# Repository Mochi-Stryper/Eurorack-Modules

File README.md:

# Eurorack-Modules
 Eurorack-Modules

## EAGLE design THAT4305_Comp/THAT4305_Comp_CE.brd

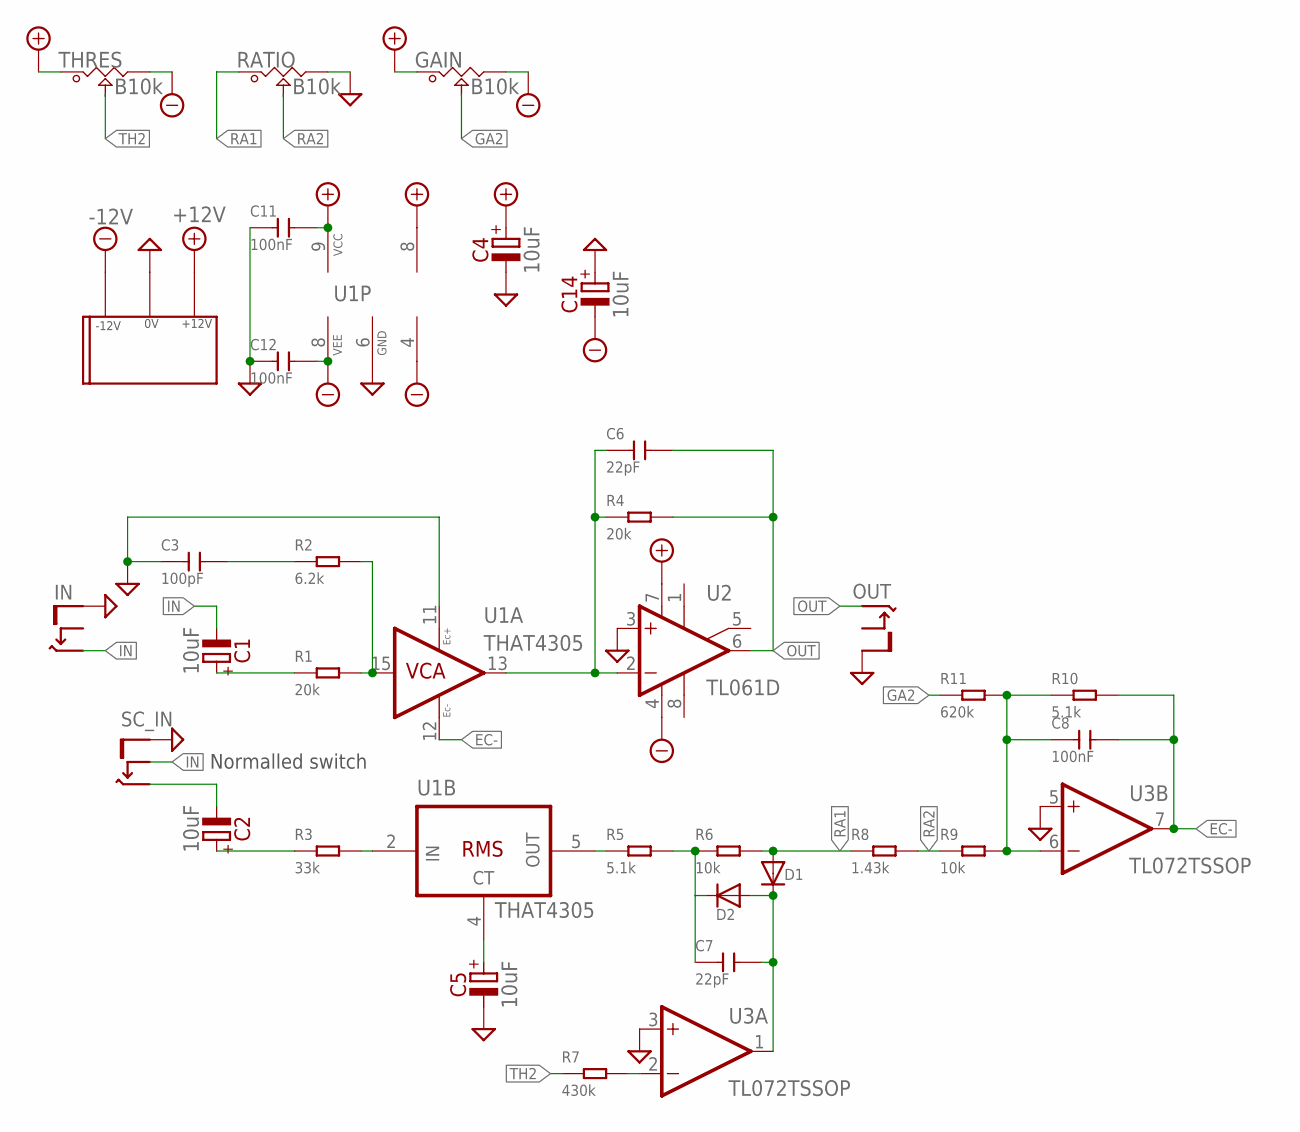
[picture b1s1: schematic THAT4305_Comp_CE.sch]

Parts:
C1, C2, C4, C5, C14: 10uF; PAN_B
C3: 100pF; C0805
C6, C7: 22pF; C0805
C8, C11, C12: 100nF; C0805
D1, D2: DIODESOD-123; SOD-123
GAIN: B10k; POT_9MM_SMD
R1, R4: 20k; R0805
R2: 6.2k; R0805
R3: 33k; R0805
R5, R10: 5.1k; R0805
R6, R9: 10k; R0805
R7: 430k; R0805
R8: 1.43k; R0805
R11: 620k; R0805
RATIO: B10k; POT_9MM_SMD
THRES: B10k; POT_9MM_SMD
U1: THAT4305; QSOP16
U2: TL061D; SO08
U3: TL072TSSOP; TSSOP-8
U$2: EURO_POW_CEH
U$3: THONKICONN_CE_3X_COMG_1SW; 1.27MM_CE_4X_COMG_NOSW

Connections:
+12V: C4.1+ (+), C11.2, GAIN.1, THRES.1, U1.9 (VCC), U2.7 (V+), U3.8 (V+), U$2.+12V
-12V: C12.2, C14.2- (-), GAIN.3, THRES.3, U1.8 (VEE), U2.4 (V-), U3.4 (V-), U$2.-12V
EC-: C8.2, R10.2, U1.12 (EC-), U3.7 (OUT)
GA2: GAIN.2, R11.1
GND: C3.1, C4.2- (-), C5.2- (-), C11.1, C12.1, C14.1+ (+), RATIO.3, U1.6 (GND), U1.11 (EC+), U2.3 (+IN), U3.3 (+IN), U3.5 (+IN), U$2.GND, U$3.0 (S)
IN: C1.2- (-), U$3.2 (SW), U$3.3 (T)
unnamed: C1.1+ (+), R1.1
unnamed: C3.2, R2.1
unnamed: R1.2, R2.2, U1.15 (VCA_IN)
unnamed: C2.1+ (+), R3.1
unnamed: R3.2, U1.2 (RMS_IN)
unnamed: C5.1+ (+), U1.4 (CT)
unnamed: C6.1, R4.1, U1.13 (VCA_OUT), U2.2 (-IN)
unnamed: R5.1, U1.5 (RMS_OUT)
unnamed: C7.1, D2.C, R5.2, R6.1
unnamed: C8.1, R9.2, R10.1, R11.2, U3.6 (-IN)
unnamed: C7.2, D1.C, D2.A, U3.1 (OUT)
unnamed: R7.2, U3.2 (-IN)
OUT: C6.2, R4.2, U2.6 (OUT), U$3.4 (T)
RA1: D1.A, R6.2, R8.1, RATIO.1
RA2: R8.2, R9.1, RATIO.2
SC_IN: C2.2- (-), U$3.1 (T)
TH2: R7.1, THRES.2

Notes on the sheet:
SC_IN
OUT
Normalled switch

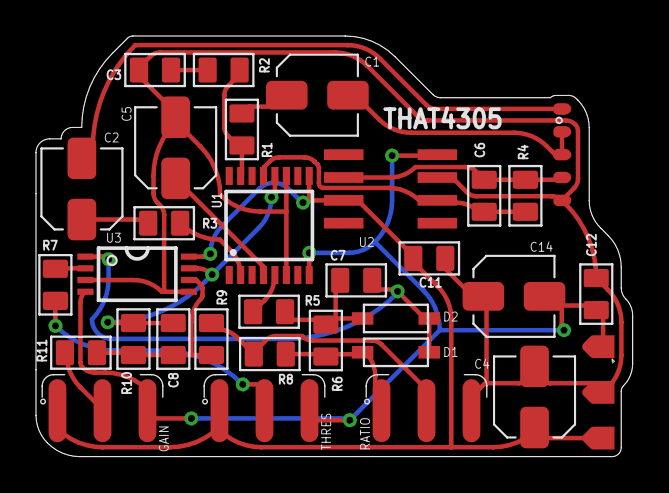
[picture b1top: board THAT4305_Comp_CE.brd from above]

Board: 2 copper layers, 33.1 x 23.4 mm, 32 parts (0 on the bottom side), 23 nets.

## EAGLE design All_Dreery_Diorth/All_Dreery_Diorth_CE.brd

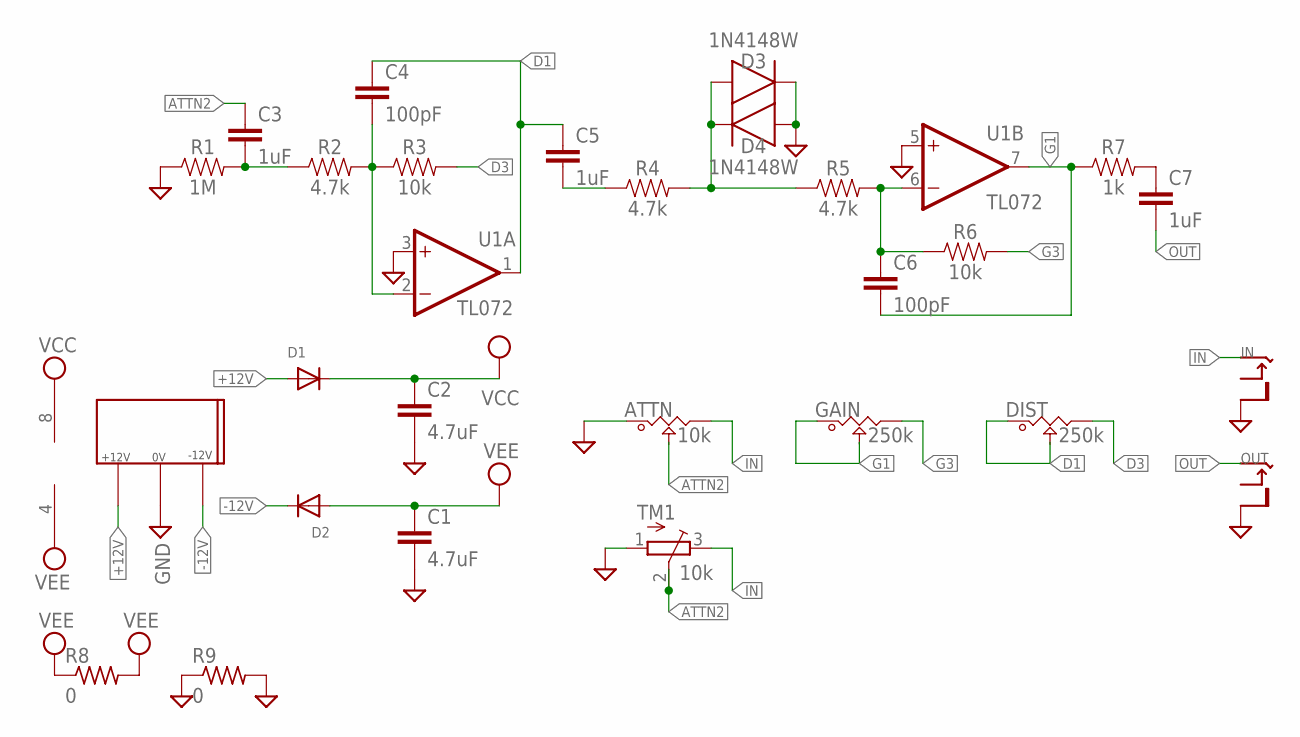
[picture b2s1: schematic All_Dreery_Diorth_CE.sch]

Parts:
ATTN: 10k; POT_9MM_SMD
C1, C2: 4.7uF; 1206
C3, C5, C7: 1uF; 0603
C4, C6: 100pF; 0603
D1, D2: DIODESOD-123; SOD-123
D3, D4: 1N4148W; SOD3715X135
DIST: 250k; POT_9MM_SMD
GAIN: 250k; POT_9MM_SMD
R1: 1M; 0603
R2, R4, R5: 4.7k; 0603
R3, R6: 10k; 0603
R7: 1k; 0603
R8, R9: 0; R0402
TM1: 10k; TC33X
U1: TL072; TSSOP-8
U$1: EURO_POW_CEH
U$2: THONKICONN_CE_2X_COMG_NOSW; 1.27MM_CE_2X_COMG_NOSW

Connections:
+12V: D1.A, U$1.+12V
-12V: D2.C, U$1.-12V
ATTN2: ATTN.2, C3.1, TM1.2 (S)
D1: C4.1, C5.1, DIST.1, DIST.2, U1.1 (OUT)
D3: DIST.3, R3.2
G1: C6.2, GAIN.1, GAIN.2, R7.1, U1.7 (OUT)
G3: GAIN.3, R6.2
GND: ATTN.1, C1.2, C2.2, D3.1 (C), D4.2 (A), R1.1, R9.1, R9.2, TM1.1 (A), U1.3 (+IN), U1.5 (+IN), U$1.GND, U$2.0 (S)
IN: ATTN.3, TM1.3 (E), U$2.1 (T)
unnamed: C3.2, R1.2, R2.1
unnamed: C4.2, R2.2, R3.1, U1.2 (-IN)
unnamed: C7.1, R7.2
unnamed: C5.2, R4.1
unnamed: D3.2 (A), D4.1 (C), R4.2, R5.1
unnamed: C6.1, R5.2, R6.1, U1.6 (-IN)
OUT: C7.2, U$2.2 (T)
VCC: C2.1, D1.C, U1.8 (V+)
VEE: C1.1, D2.A, R8.1, R8.2, U1.4 (V-)

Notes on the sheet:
OUT

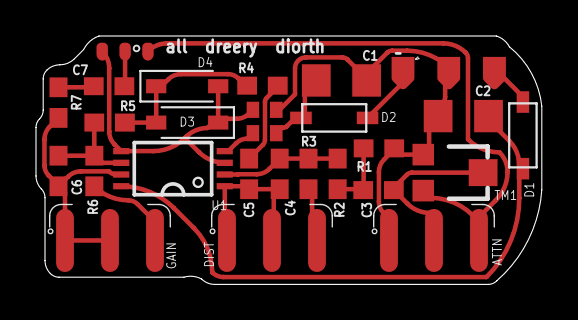
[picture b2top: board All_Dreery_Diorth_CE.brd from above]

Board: 2 copper layers, 28.1 x 13.8 mm, 27 parts (0 on the bottom side), 18 nets.

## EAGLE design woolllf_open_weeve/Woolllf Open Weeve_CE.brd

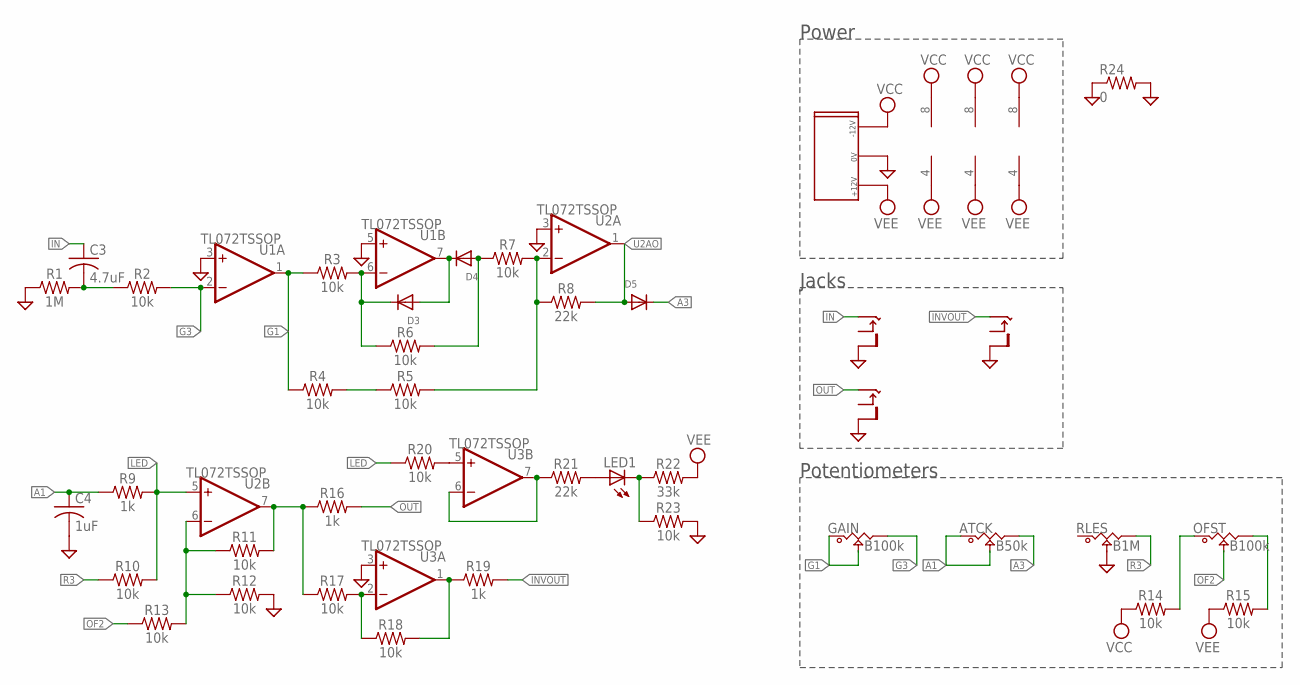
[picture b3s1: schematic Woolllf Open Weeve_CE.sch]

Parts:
ATCK: B50k; POT_9MM_SMD
C3: 4.7uF; C0603
C4: 1uF; C0603
D3, D4, D5: DIODESOD-123; SOD-123
GAIN: B100k; POT_9MM_SMD
LED1: LEDCHIP-LED0603; CHIP-LED0603
OFST: B100k; POT_9MM_SMD
R1: 1M; 0603
R2, R3, R4, R5, R6, R7, R10, R11, R12, R13, R14, R15, R17, R18, R20, R23: 10k; 0603
R8, R21: 22k; 0603
R9, R16, R19: 1k; 0603
R22: 33k; 0603
R24: 0; R0402
RLES: B1M; POT_9MM_SMD
U1, U2, U3: TL072TSSOP; TSSOP-8
U$1: EURO_POW_CEH
U$2: THONKICONN_CE_3X_COMG_NOSW; 1.27MM_CE_3X_COMG_NOSW

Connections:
A1: ATCK.1, ATCK.2, C4.1, R9.1
A3: ATCK.3, D5.C
G1: GAIN.1, GAIN.2, R3.1, R4.1, U1.1 (OUT)
G3: GAIN.3, R2.2, U1.2 (-IN)
GND: C4.2, R1.1, R12.2, R23.2, R24.1, R24.2, RLES.2, U1.3 (+IN), U1.5 (+IN), U2.3 (+IN), U3.3 (+IN), U$1.GND, U$2.0 (S)
IN: C3.1, U$2.1 (T)
INVOUT: R19.2, U$2.2 (T)
LED: R9.2, R10.2, R20.1, U2.5 (+IN)
unnamed: LED1.A, R21.2
unnamed: C3.2, R1.2, R2.1
unnamed: D3.C, R3.2, R6.1, U1.6 (-IN)
unnamed: D3.A, D4.C, U1.7 (OUT)
unnamed: D4.A, R6.2, R7.1
unnamed: R20.2, U3.5 (+IN)
unnamed: R4.2, R5.1
unnamed: R5.2, R7.2, R8.1, U2.2 (-IN)
unnamed: R11.1, R12.1, R13.2, U2.6 (-IN)
unnamed: R11.2, R16.1, R17.1, U2.7 (OUT)
unnamed: OFST.1, R14.2
unnamed: OFST.3, R15.2
unnamed: R17.2, R18.1, U3.2 (-IN)
unnamed: R18.2, R19.1, U3.1 (OUT)
unnamed: R21.1, U3.6 (-IN), U3.7 (OUT)
unnamed: LED1.C, R22.1, R23.1
OF2: OFST.2, R13.1
OUT: R16.2, U$2.3 (T)
R3: R10.1, RLES.3
U2AO: D5.A, R8.2, U2.1 (OUT)
VCC: R14.1, U1.8 (V+), U2.8 (V+), U3.8 (V+), U$1.-12V
VEE: R15.1, R22.2, U1.4 (V-), U2.4 (V-), U3.4 (V-), U$1.+12V

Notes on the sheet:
Power
Jacks
Potentiometers

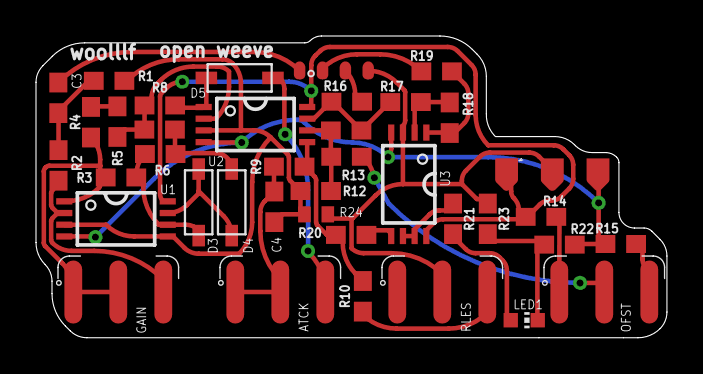
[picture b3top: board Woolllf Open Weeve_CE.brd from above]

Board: 2 copper layers, 35.1 x 16.8 mm, 39 parts (0 on the bottom side), 30 nets.

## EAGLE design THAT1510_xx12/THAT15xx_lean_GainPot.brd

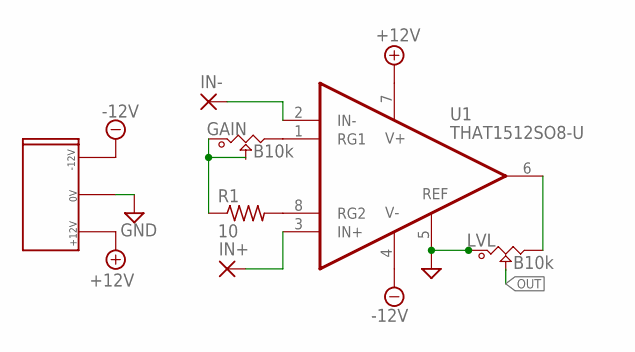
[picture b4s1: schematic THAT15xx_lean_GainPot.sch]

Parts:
GAIN: B10k; POT_9MM_SMD
IN+: WIREPADSMD5-1,8; 5-1,8
IN-: WIREPADSMD5-1,8; 5-1,8
LVL: B10k; POT_9MM_SMD
R1: 10; R0603
U1: THAT1512SO8-U; SO08
U$1: EURO_POW_CEH

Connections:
15XXO: LVL.3, U1.6 (OUT)
+12V: U1.7 (V+), U$1.+12V
-12V: U1.4 (V-), U$1.-12V
GND: LVL.1, U1.5 (REF), U$1.GND
IN+: IN+.1, U1.3 (IN+)
IN-: IN-.1, U1.2 (IN-)
unnamed: R1.2, U1.8 (RG2)
unnamed: GAIN.3, U1.1 (RG1)
unnamed: GAIN.1, GAIN.2, R1.1
OUT: LVL.2

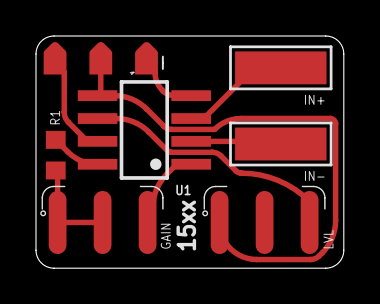
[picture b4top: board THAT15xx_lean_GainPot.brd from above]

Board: 2 copper layers, 17.1 x 12.9 mm, 7 parts (0 on the bottom side), 9 nets.

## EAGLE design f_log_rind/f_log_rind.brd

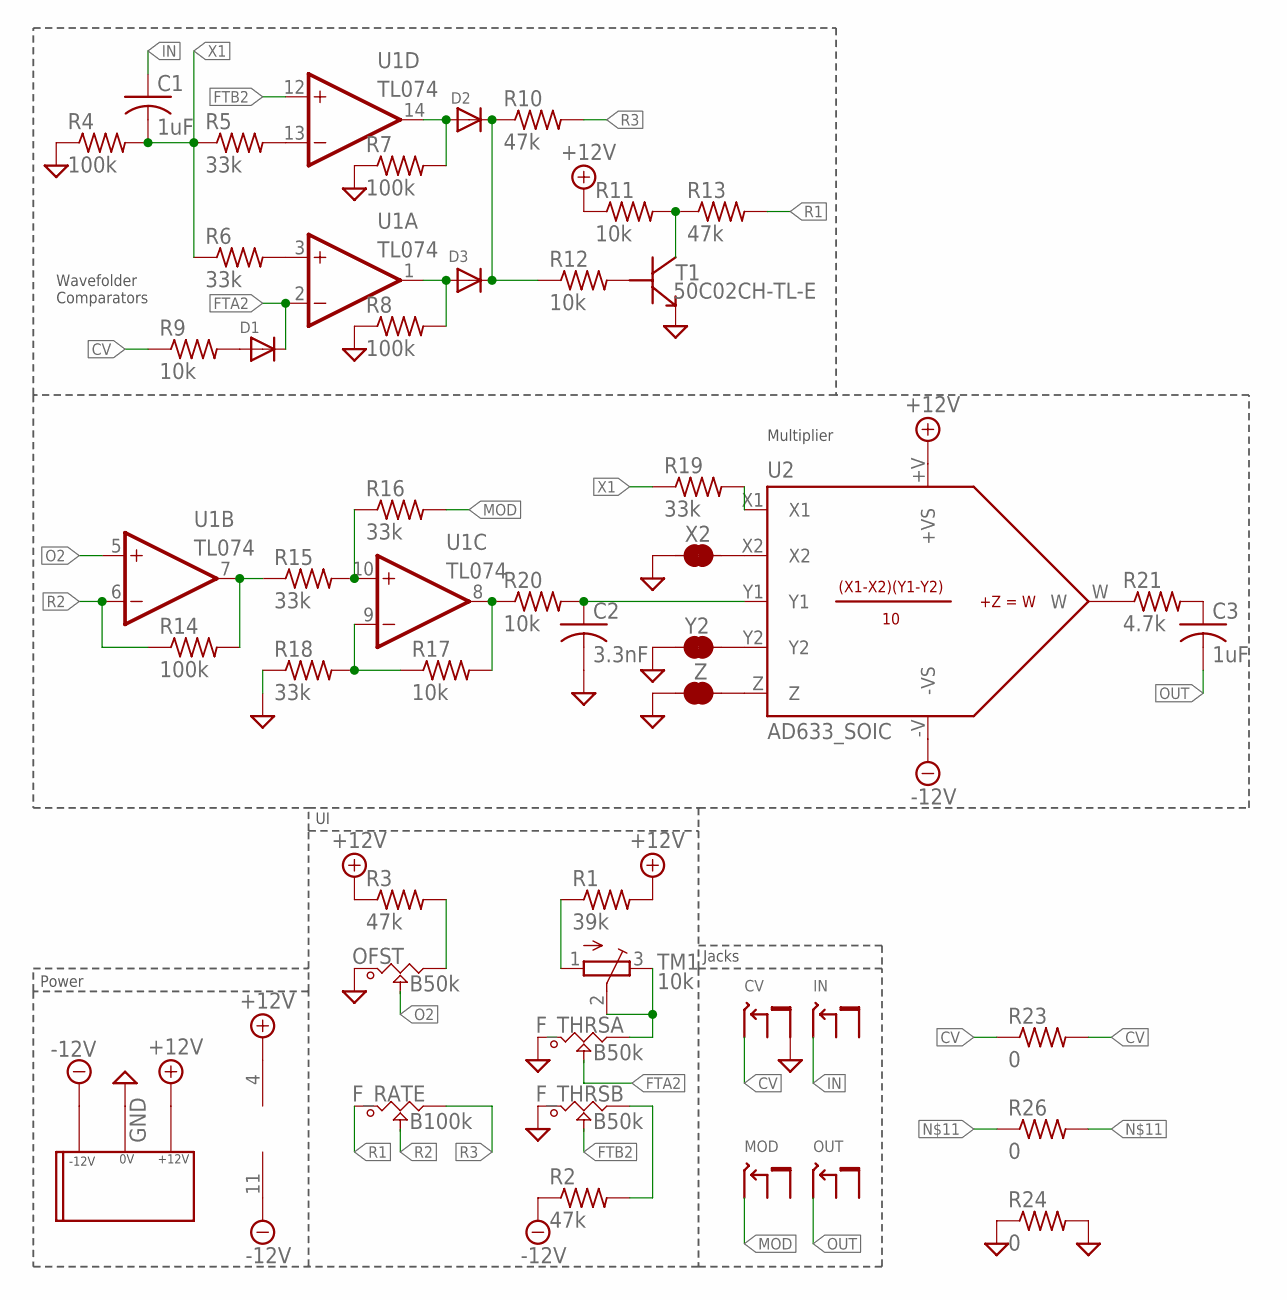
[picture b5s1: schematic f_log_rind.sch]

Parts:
C1, C3: 1uF; C0603
C2: 3.3nF; C0603
D1, D2, D3: DIODESOD-123; SOD-123
F_RATE: B100k; POT_9MM_SMD
F_THRSA: B50k; POT_9MM_SMD
F_THRSB: B50k; POT_9MM_SMD
J_A1: THONKICONN_CE_4X_COMG_NOSW; 1.27MM_CE_4X_COMG_NOSW
OFST: B50k; POT_9MM_SMD
R1: 39k; R0603
R2, R3, R10, R13: 47k; R0603
R4, R7, R8, R14: 100k; R0603
R5, R6, R15, R16, R18, R19: 33k; R0603
R9, R11, R12, R17, R20: 10k; R0603
R21: 4.7k; R0603
R23, R24, R26: 0; R0402
T1: 50C02CH-TL-E; BEC
TM1: 10k; TC33X
U1: TL074; SO14
U2: AD633_SOIC; SOIC_8
U$1: EURO_POW_CEH
X2: JUMPER-SMT_2_NC_TRACE_NO-SILK; SMT-JUMPER_2_NC_TRACE_NO-SILK
Y2: JUMPER-SMT_2_NC_TRACE_NO-SILK; SMT-JUMPER_2_NC_TRACE_NO-SILK
Z: JUMPER-SMT_2_NC_TRACE_NO-SILK; SMT-JUMPER_2_NC_TRACE_NO-SILK

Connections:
+12V: R1.2, R3.1, R11.1, U1.4 (V+), U2.+V (+VS), U$1.+12V
-12V: R2.1, U1.11 (V-), U2.-V (-VS), U$1.-12V
A1A+: R6.2, U1.3 (+IN)
A1AO: D3.A, R8.2, U1.1 (OUT)
A1BO: R14.2, R15.1, U1.7 (OUT)
A1C+: R15.2, R16.1, U1.10 (+IN)
A1C-: R17.1, R18.2, U1.9 (-IN)
A1CO: R17.2, R20.1, U1.8 (OUT)
A1D-: R5.2, U1.13 (-IN)
A1DO: D2.A, R7.2, U1.14 (OUT)
CV: J_A1.1 (T), R9.1, R23.1, R23.2
FTA2: D1.C, F_THRSA.2, U1.2 (-IN)
FTB2: F_THRSB.2, U1.12 (+IN)
GND: C2.2, F_THRSA.1, F_THRSB.1, J_A1.0 (S), OFST.1, R4.1, R7.1, R8.1, R18.1, R24.1, R24.2, T1.E, U$1.GND, X2.1, Y2.1, Z.1
IN: C1.1, J_A1.2 (T)
MOD: J_A1.3 (T), R16.2
unnamed: F_THRSA.3, TM1.2 (S), TM1.3 (E)
unnamed: R1.1, TM1.1 (A)
unnamed: F_THRSB.3, R2.2
unnamed: OFST.3, R3.2
unnamed: U2.Z, Z.2
unnamed: R21.1, U2.W
unnamed: C3.1, R21.2
unnamed: D1.A, R9.2
unnamed: D2.C, D3.C, R10.1, R12.1, R26.1, R26.2
unnamed: R12.2, T1.B
unnamed: R11.2, R13.1, T1.C
unnamed: U2.Y2, Y2.2
unnamed: U2.X2, X2.2
unnamed: R19.2, U2.X1
O2: OFST.2, U1.5 (+IN)
OUT: C3.2, J_A1.4 (T)
R1: F_RATE.1, R13.2
R2: F_RATE.2, R14.1, U1.6 (-IN)
R3: F_RATE.3, R10.2
X1: C1.2, R4.2, R5.1, R6.1, R19.1
Y1: C2.1, R20.2, U2.Y1

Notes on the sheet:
MOD
OUT
Power
Jacks
Wavefolder Comparators
Multiplier

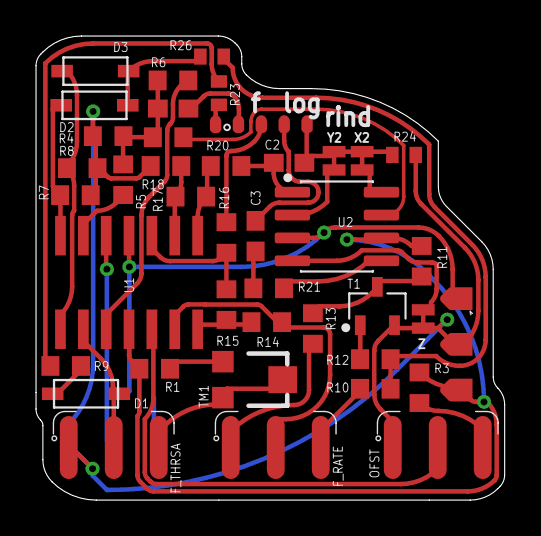
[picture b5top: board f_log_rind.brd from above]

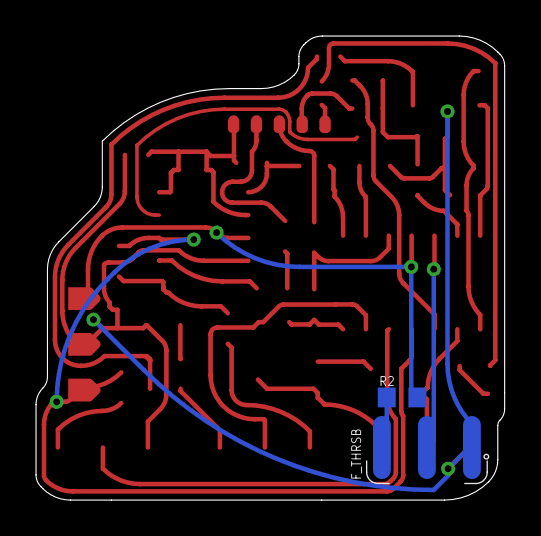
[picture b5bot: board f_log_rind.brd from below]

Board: 2 copper layers, 26.0 x 25.8 mm, 43 parts (2 on the bottom side), 37 nets.

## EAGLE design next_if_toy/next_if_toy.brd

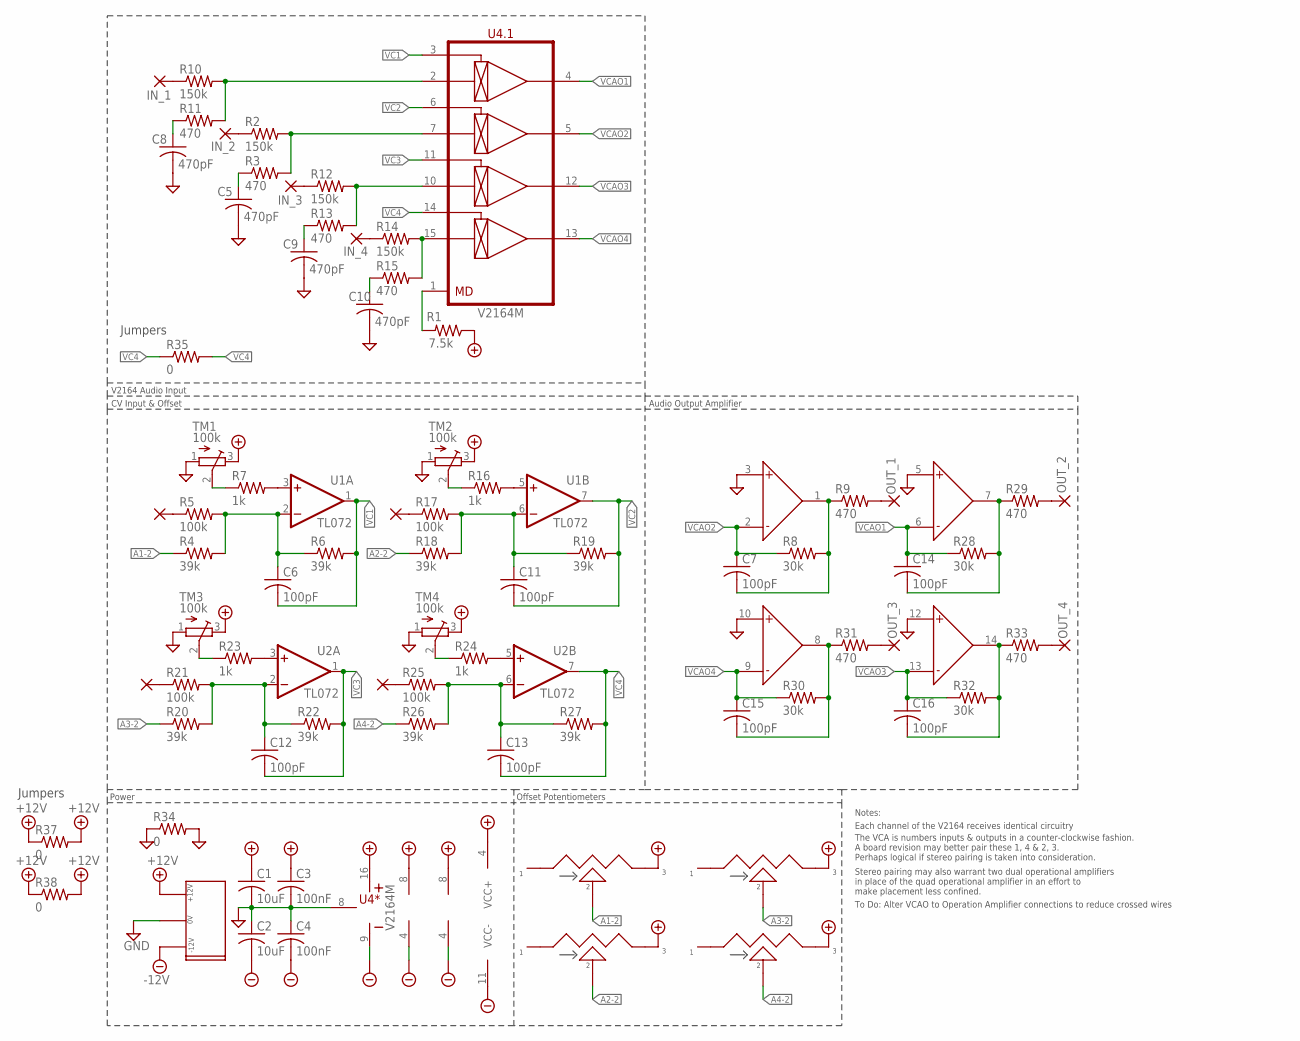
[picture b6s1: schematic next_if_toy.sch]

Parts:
AMT1, AMT2, AMT3, AMT4: B50k; POT_9MM_SMD
C1, C2: 10uF; C1206
C3, C4: 100nF; C0603
C5, C8, C9, C10: 470pF; C0603
C6, C7, C11, C12, C13, C14, C15, C16: 100pF; C0603
CV1, CV2, CV3, CV4: SMD2; SMD1,27-2,54
I1, I2, I3, I4: SMD2; SMD1,27-2,54
O1, O2, O3, O4: SMD2; SMD1,27-2,54
R1: 7.5k; R0603
R2, R10, R12, R14: 150k; R0603
R3, R9, R11, R13, R15, R29, R31, R33: 470; R0603
R4, R6, R18, R19, R20, R22, R26, R27: 39k; R0603
R5, R17, R21, R25: 100k; R0603
R7, R16, R23, R24: 1k; R0603
R8, R28, R30, R32: 30k; R0603
R34, R35, R37, R38: 0; R0402
TM1, TM2, TM3, TM4: 100k; TC33X
U1, U2: TL072; TSSOP-8
U3: TL074TSSOP-14
U4: V2164M; SO-16
U$2: EURO_POW_CEH

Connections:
+12V: AMT1.3, AMT2.3, AMT3.3, AMT4.3, C1.1, C3.1, R1.1, R37.1, R37.2, R38.1, R38.2, TM1.3 (E), TM2.3 (E), TM3.3 (E), TM4.3 (E), U1.8 (V+), U2.8 (V+), U3.4 (VCC+), U4.16 (V+), U$2.+12V
-12V: C2.2, C4.2, U1.4 (V-), U2.4 (V-), U3.11 (VCC-), U4.9 (V-), U$2.-12V
A1-2: AMT1.2, R4.1
A2-2: AMT2.2, R18.1
A3-2: AMT3.2, R20.1
A4-2: AMT4.2, R26.1
GND: C1.2, C2.1, C3.2, C4.1, C5.2, C8.2, C9.2, C10.2, R34.1, R34.2, TM1.1 (A), TM2.1 (A), TM3.1 (A), TM4.1 (A), U3.3 (I+), U3.5 (I+), U3.10 (I+), U3.12 (I+), U4.8 (GND), U$2.GND
I-1: C6.1, R4.2, R5.2, R6.1, U1.2 (-IN)
I-2: C11.1, R17.2, R18.2, R19.1, U1.6 (-IN)
I-3: C12.1, R20.2, R21.2, R22.1, U2.2 (-IN)
I-4: C13.1, R25.2, R26.2, R27.1, U2.6 (-IN)
MODE: R1.2, U4.1 (MD)
unnamed: C5.1, R3.1
unnamed: C8.1, R11.1
unnamed: C9.1, R13.1
unnamed: CV1.1, R5.1
unnamed: C10.1, R15.1
unnamed: R7.2, U1.3 (+IN)
unnamed: R16.2, U1.5 (+IN)
unnamed: CV2.1, R17.1
unnamed: R23.2, U2.3 (+IN)
unnamed: R24.2, U2.5 (+IN)
unnamed: CV3.1, R21.1
unnamed: CV4.1, R25.1
OUT_1: O1.1, R9.2
OUT_2: O2.1, R29.2
OUT_3: O3.1, R31.2
OUT_4: O4.1, R33.2
SJI_1: I1.1, R10.1
SJI_2: I2.1, R2.1
SJI_3: I3.1, R12.1
SJI_4: I4.1, R14.1
T1: R7.1, TM1.2 (S)
T2: R16.1, TM2.2 (S)
T3: R23.1, TM3.2 (S)
T4: R24.1, TM4.2 (S)
U3O1: C7.2, R8.2, R9.1, U3.1 (O)
U3O2: C14.2, R28.2, R29.1, U3.7 (O)
U3O3: C15.2, R30.2, R31.1, U3.8 (O)
U3O4: C16.2, R32.2, R33.1, U3.14 (O)
VC1: C6.2, R6.2, U1.1 (OUT), U4.3 (CV1)
VC2: C11.2, R19.2, U1.7 (OUT), U4.6 (CV2)
VC3: C12.2, R22.2, U2.1 (OUT), U4.11 (CV3)
VC4: C13.2, R27.2, R35.1, R35.2, U2.7 (OUT), U4.14 (CV4)
VCAI1: R10.2, R11.2, U4.2 (IN1)
VCAI2: R2.2, R3.2, U4.7 (IN2)
VCAI3: R12.2, R13.2, U4.10 (IN3)
VCAI4: R14.2, R15.2, U4.15 (IN4)
VCAO1: C14.1, R28.1, U3.6 (I-), U4.4 (OUT1)
VCAO2: C7.1, R8.1, U3.2 (I-), U4.5 (OUT2)
VCAO3: C16.1, R32.1, U3.13 (I-), U4.12 (OUT3)
VCAO4: C15.1, R30.1, U3.9 (I-), U4.13 (OUT4)

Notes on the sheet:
V2164 Audio Input
CV Input & Offset
Power
Offset Potentiometers
Audio Output Amplifier
Notes:
Each channel of the V2164 receives identical circuitry
The VCA is numbers inputs & outputs in a counter-clockwise fashion. A board revision may better pair these 1, 4 & 2, 3. Perhaps logical if stereo pairing is taken into consideration.
Stereo pairing may also warrant two dual operational amplifiers in place of the quad operational amplifier in an effort to make placement less confined.
To Do: Alter VCAO to Operation Amplifier connections to reduce crossed wires
IN_1
IN_2
IN_3
IN_4
OUT_1
OUT_2
OUT_3
OUT_4
Jumpers

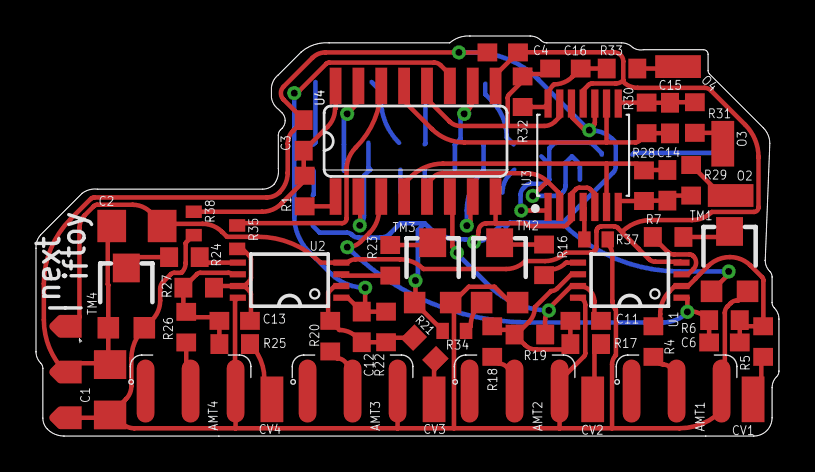
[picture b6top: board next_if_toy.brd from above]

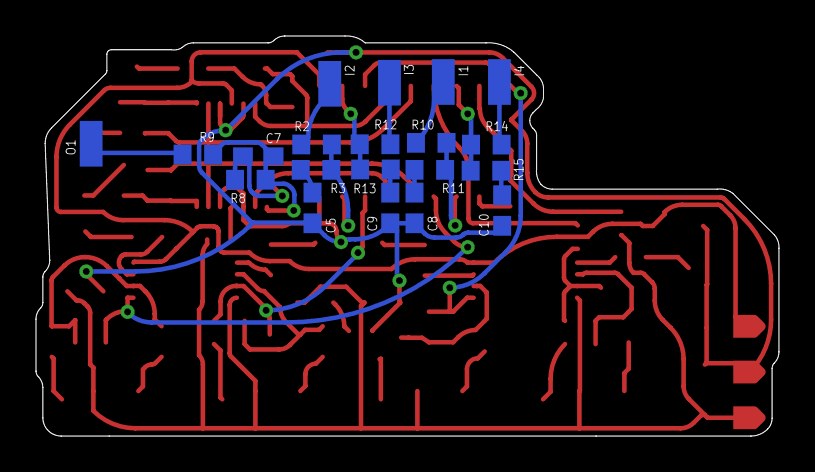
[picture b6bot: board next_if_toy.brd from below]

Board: 2 copper layers, 41.3 x 22.2 mm, 78 parts (20 on the bottom side), 52 nets.

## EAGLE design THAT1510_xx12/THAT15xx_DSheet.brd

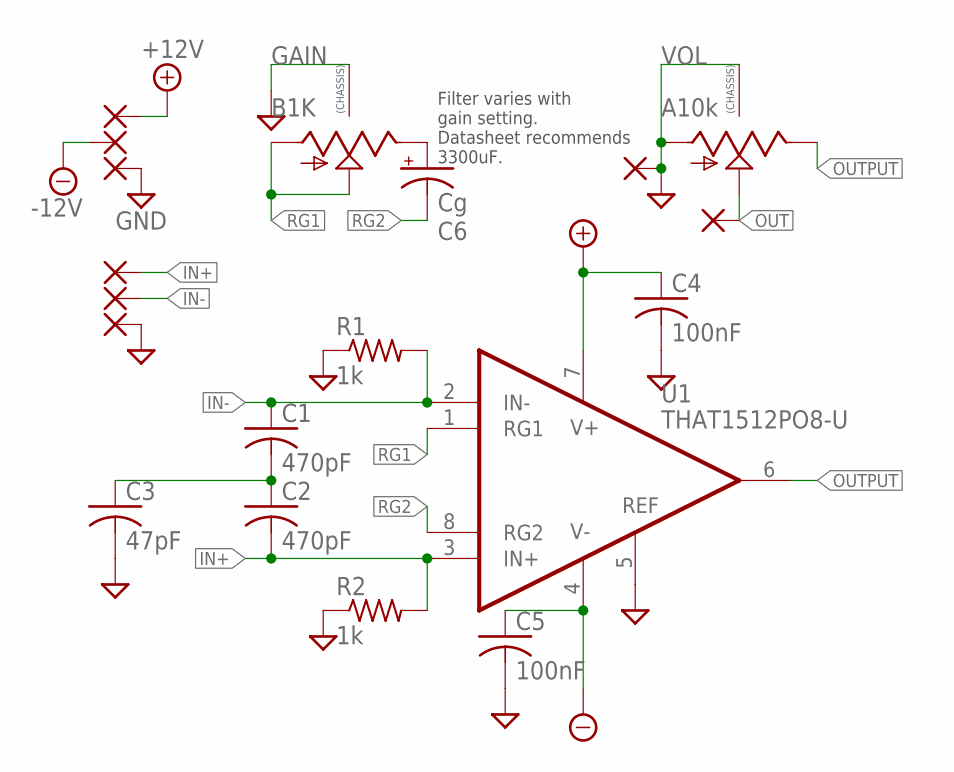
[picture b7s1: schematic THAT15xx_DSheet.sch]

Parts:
C1, C2: 470pF; C0805
C3: 47pF; C0805
C4, C5: 100nF; C0805
C6: Cg; PAN_C_SMD+THRU
GAIN: B1K; 9MM_SNAP-IN_POT
PAD1, PAD2, PAD3, PAD4, PAD5, PAD6, PAD7, PAD8: WIREPAD1,6/0,9; 1,6/0,9
R1, R2: 1k; R0805
U1: THAT1512PO8-U; DIL08
VOL: A10k; 9MM_SNAP-IN_POT

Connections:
+12V: C4.1, PAD3.1, U1.7 (V+)
-12V: C5.1, PAD1.1, U1.4 (V-)
GND: C3.2, C4.2, C5.2, GAIN.CHASSIS1, GAIN.CHASSIS2, PAD2.1, PAD6.1, PAD7.1, R1.1, R2.1, U1.5 (REF), VOL.1 (A), VOL.CHASSIS1, VOL.CHASSIS2
IN+: C2.2, PAD4.1, R2.2, U1.3 (IN+)
IN-: C1.1, PAD5.1, R1.2, U1.2 (IN-)
unnamed: C1.2, C2.1, C3.1
unnamed: C6.+, C6.++ (+), GAIN.3 (E)
OUT: PAD8.1, VOL.2 (S)
OUTPUT: U1.6 (OUT), VOL.3 (E)
RG1: GAIN.1 (A), GAIN.2 (S), U1.1 (RG1)
RG2: C6.-, C6.-- (-), U1.8 (RG2)

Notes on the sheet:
Filter varies with gain setting. Datasheet recommends 3300uF.

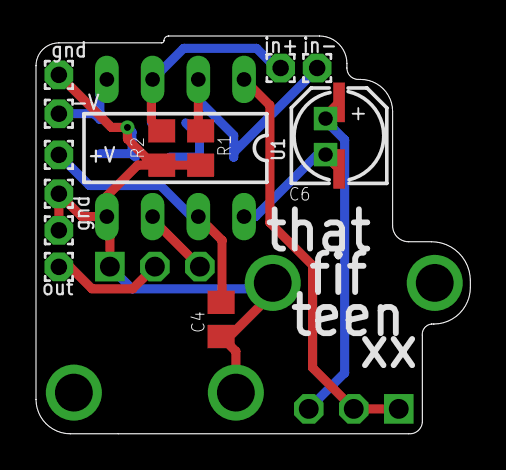
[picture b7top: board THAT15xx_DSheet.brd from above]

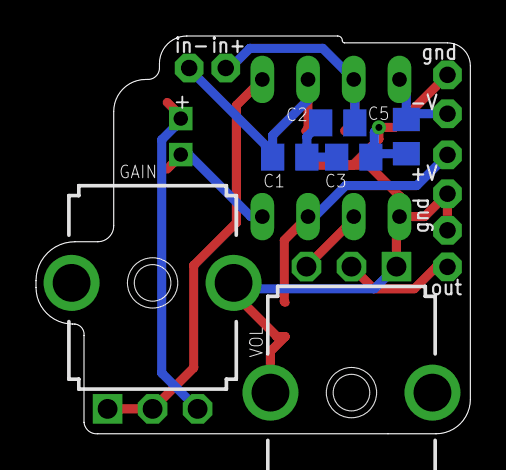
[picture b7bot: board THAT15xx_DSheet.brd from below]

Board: 2 copper layers, 24.1 x 22.1 mm, 19 parts (6 on the bottom side), 11 nets.

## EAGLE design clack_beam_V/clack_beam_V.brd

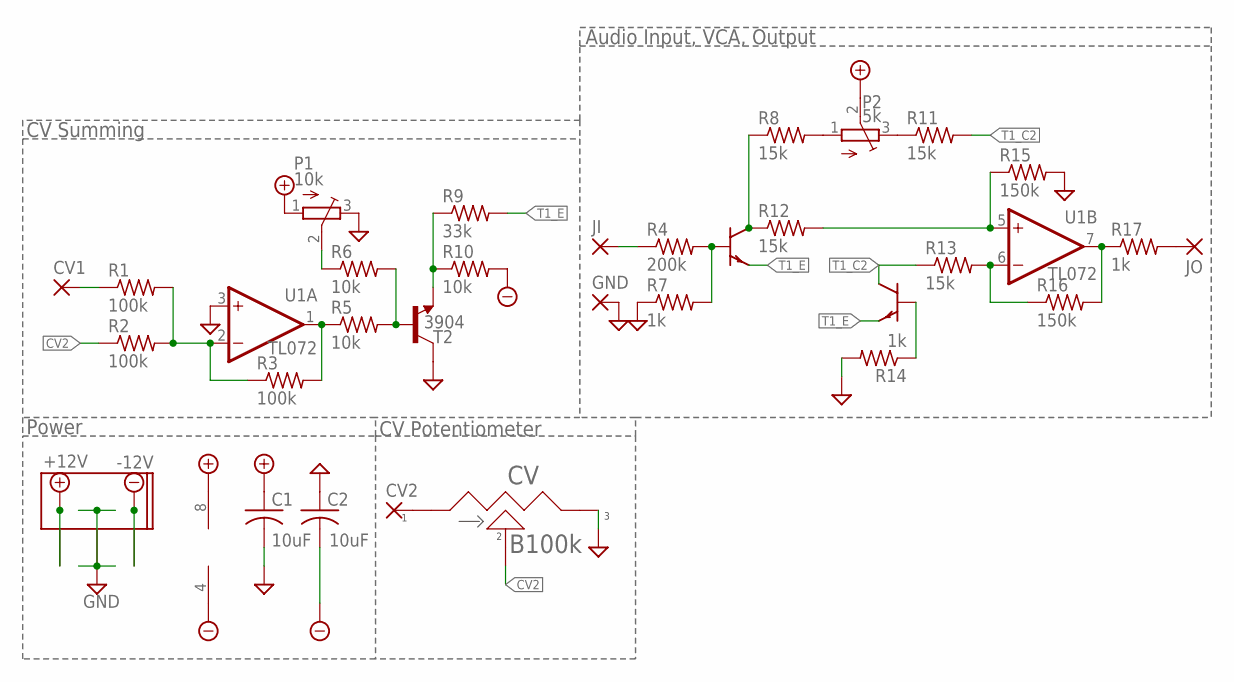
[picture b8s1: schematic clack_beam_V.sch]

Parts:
C1, C2: 10uF; C1206
CV: B100k; POT_9MM_SMD
CV1, CV2: WIREPADSMD1,27-254; SMD1,27-2,54
GND: WIREPADSMD1,27-254; SMD1,27-2,54
JI: WIREPADSMD1,27-254; SMD1,27-2,54
JO: WIREPADSMD1,27-254; SMD1,27-2,54
P1: 10k; TC33X
P2: 5k; TC33X
R1, R2, R3: 100k; R0603
R4: 200k; R0603
R5, R6, R10: 10k; R0603
R7, R14, R17: 1k; R0603
R8, R11, R12, R13: 15k; R0603
R9: 33k; R0603
R15, R16: 150k; R0603
T1: MBT3904DW1; MBT3904DW1T1G
T2: 3904; SOT23-BEC
U1: TL072; TSSOP-8
U$1: EURO_POW_SMD

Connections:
1AI-: R1.2, R2.2, R3.1, U1.2 (-IN)
1AO: R3.2, R5.1, U1.1 (OUT)
2AI+: R12.2, R15.1, U1.5 (+IN)
2AO: R16.2, R17.1, U1.7 (OUT)
2_AI-: R13.2, R16.1, U1.6 (-IN)
+12V: C1.1, P1.1 (A), P2.2 (S), U1.8 (V+), U$1.P$9, U$1.P$10
-12V: C2.2, R10.2, U1.4 (V-), U$1.P$1, U$1.P$2
CV1: CV1.1, R1.1
CV2: CV.2, R2.1
CV2_I: CV.1, CV2.1
GND: C1.2, C2.1, CV.3, GND.1, P1.3 (E), R7.1, R14.2, R15.2, T2.C, U1.3 (+IN), U$1.P$3, U$1.P$4, U$1.P$5, U$1.P$6, U$1.P$7, U$1.P$8
JI: JI.1, R4.1
JO: JO.1, R17.2
unnamed: P1.2 (S), R6.1
unnamed: P2.1 (A), R8.2
unnamed: P2.3 (E), R11.1
T1_B1: R4.2, R7.2, T1.5 (B)
T1_B2: R14.1, T1.2 (B)
T1_C1: R8.1, R12.1, T1.3 (C)
T1_C2: R11.2, R13.1, T1.6 (C)
T1_E: R9.2, T1.1 (E), T1.4 (E)
T2_B: R5.2, R6.2, T2.B
T2_E: R9.1, R10.1, T2.E

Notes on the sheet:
B100k
CV Summing
CV Potentiometer
Audio Input, VCA, Output
Power

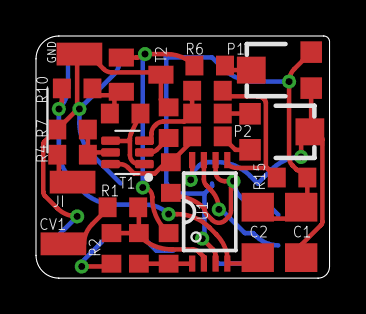
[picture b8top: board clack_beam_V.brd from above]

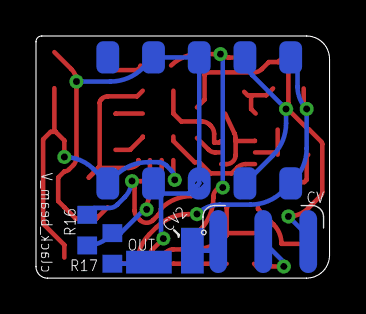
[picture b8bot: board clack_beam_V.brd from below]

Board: 2 copper layers, 16.3 x 13.5 mm, 31 parts (6 on the bottom side), 23 nets.

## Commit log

2020-09-29 Deleted Redundancies
    Deleted Redundancies
2021-04-20 Added doorman_adult_rig
    Added doorman_adult_rig, a ring mod based on the AD633
2021-04-20 Added V2153 Breakout
    Added V2153 Breakout
2021-04-24 added mercklaB_4305
    added mercklaB_4305
2021-04-25 Added 15xx_Dfrntl_Preamp
    Added 15xx_Dfrntl_Preamp
2022-04-04 Added clack_beam_V
    Added clack_beam_V
2022-05-01 Added THAT15xx
    Added THAT15xx
2022-05-01 Added next_if_toy
    Added next_if_toy
2022-05-01 Added f_log_rind
    Added f_log_rind
2022-05-02 Added thonkiconn_array
    Added thonkiconn_array
2022-05-07 Added THAT15xx_lean_GainPot
    Added THAT15xx_lean_GainPot
2022-05-07 Added all_dreery_diorth
    Added all_dreery_diorth
2022-05-08 Added woolllf_open_weeve
    Added woolllf_open_weeve
2022-05-08 Updated All_Dreery_Diorth
    Updated All_Dreery_Diorth
2022-05-09 Added THAT4305_CE
    Added THAT4305_CE

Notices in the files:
parts and their libraries:
SparkFun-Capacitors: Licensing: Creative Commons ShareAlike 4.0 International - https://creativecommons.org/licenses/by-sa/4.0
that-corp: Copyright (C) 2008-2010, Bob Starr
